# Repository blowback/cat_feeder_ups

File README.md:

# UPS for SureFeed Microchip Pet Feeder Connect

The feeder takes 4 'C' cell batteries. I have 7 feeders. Alkaline batteries 
get expensive real fast and murder the planet, and NiMH cells take an age to 
charge - you spend your whole life swapping batteries in and out of the charger.

The plan: build a miniature UPS that fits inside one of the 2xC-cell battery compartments,
and use it to maintain a 26650 LiPo in the other. Each feeder will be essentially 
mains powered (via a USB adaptor) most of the time: in the event of a power outage 
it will fail over to the battery, which should be sufficient to run it for a couple 
of weeks if necessary.

The other beauty of this approach: the battery has the capacity to handle the current 
draw (inrush and steady-state) when the motor is operating.

## Power consumption analysis

NiCad C cells are nominally 1.2V, so the pack is 4.8V nominal. At 5000mAh rated 
(let's be realistic and call it 2500mAh) and a two-week runtime, we can work out the average current draw:

Energy budget per feeder:

Pack energy: 4.8V × 2.5Ah = 12 Wh realistic
Runtime: 14 days = 336 hours
Average power: 12 Wh / 336 h ≈ 36 mW average
Average current at 4.8V: ≈ 7.5 mA average

**Average** current during motor operation was measured at 250 mA (cheap-ass bench PSU) - 
the peak current is probably 5x that.

## Physical constraints

A standard C cell is:

Diameter: 26.2mm
Length: 50.0mm

Each "slot" holds 2 × C cells stacked = 100mm long × 26.2mm diameter. 

With two slots side by side we have a compartment roughly 100mm deep × ~60mm wide × ~30mm tall (the slots sit in a tray).

### The slot geometry, precisely:

26 mm diameter circular cross-section (C-cell slot)
The usable PCB width isn't 26 mm — it's the chord of that circle at whatever depth the PCB sits. 
If the PCB sits centrally, the usable rectangle inscribed in a 26 mm circle is about 
22 mm wide × 22 mm tall, but since the slot is deep (100 mm) and we're filling it lengthwise, 
we treat the cross-section as a constraint on width only. Realistically 22 mm safe width, 
with the PCB sitting in the bottom of the cylindrical channel.

Length: 90 mm available (100 mm slot minus ~10 mm for wiring clearance to the cell)
Height (component clearance above PCB): roughly 8–10 mm before we hit the slot wall curvature

So we can't afford any big electrolytics or inductors.

## LiPo backup capacity in one C-cell slot:

A single-cell LiPo fits in one C-cell bay (≤26mm diameter, ≤100mm long) — 
cylindrical 26650 LiPo cells are 26mm × 65mm, giving around 4000–5000 mAh at 3.7V nominal = ~15–18 Wh. 

That's actually more energy than the current NiCadx! 

A flat pouch LiPo of similar volume would also work and might be easier to source (e.g. a 103450 or similar).

At 36mW average draw, a 5000mAh/3.7V LiPo = 18.5 Wh → 18.5 Wh ÷ 0.036 W ≈ 514 hours ≈ 21 days of backup. Nice.

Cat biscuits will have run out long before that!

## Proposed architecture

- a LiPo charge controller with "power path" management so that we can use the battery's capacity to absorb motor current demandss
- a boost convertor to boost the LiPo up to 5v. 

## Device selection 

After many, many false starts:

 - BQ24079  for the LiPo controller
 - TPS61235P boost convertor - fixed 5.1v output  and very minimal component controller
 - SPM5020T-1R0M inductor from TDK: nice and compact: 5x2mm, 11A Isat. 

 Those packages are all quite fiddly, and we'll prolly have to go to 0402 for the discretes. 
Maybe time to experiment with having a boardhouse stuff the board!  I'm thinking JLCB...

## JLPCB substitutions

- L1: was C408536 now C695604
- U2: was unspecified! now C140287 (has no SYSOFF pin, but is same package with a NC pad so no schematic/pcb change)
- J1: was C173752 - shouldn't be in BOM (is thru-hole)
- D2: was C2286 (RED) but we want GREEN so -> C12624
- R4, R6: wrong part, need 1.5k 0402 -> C114759
- R5: wrong part, need 10k 0402 -> C60490
- R7: wrong part, need 1.18k -> C3016052
- R8: wrong part, need 1.13k -> C453521

## JLPCB substitutions (2)

Gah, LED footprints are 0402 but the LCSC part numbers are for 0603!

- D1: (RED) -> C130719
- D2: (GREEN) -> C74338
- R8: was C453521 but JLPCB no-stocky, switching forC67014

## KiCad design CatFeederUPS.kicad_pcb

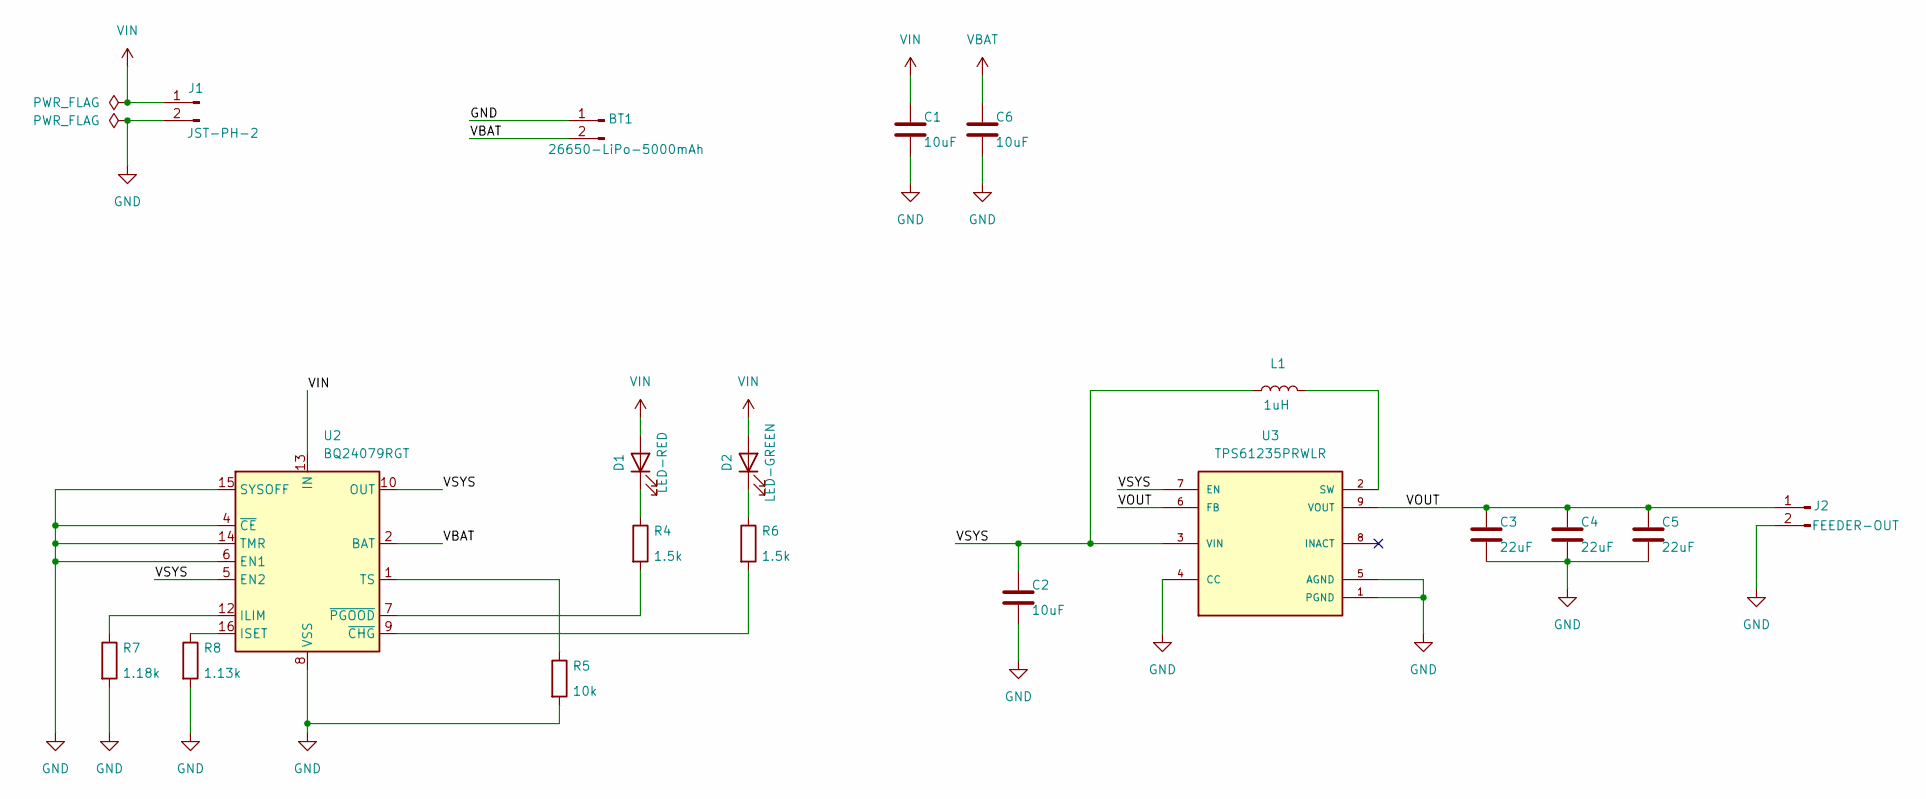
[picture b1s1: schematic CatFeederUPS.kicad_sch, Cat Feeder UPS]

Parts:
BT1: 26650-LiPo-5000mAh; PinHeader_1x02_P2.54mm_Vertical
C1, C6: 10uF; C_0402_1005Metric; Voltage 10V; LCSC C15525
C2: 10uF; C_0402_1005Metric; Voltage 6.3V; LCSC C15525
C3, C4, C5: 22uF; C_0603_1608Metric; Voltage 10V; LCSC C59461
D1: LED-RED; LED_0402_1005Metric; LCSC C130719
D2: LED-GREEN; LED_0402_1005Metric; LCSC C74338
J1: JST-PH-2; JST_PH_S2B-PH-K_1x02_P2.00mm_Horizontal
J2: FEEDER-OUT; PinHeader_1x02_P2.54mm_Vertical
L1: 1uH; IND_SPM5020T-1R0M-LR; LCSC C695604
R4, R6: 1.5k; R_0402_1005Metric; LCSC C114759
R5: 10k; R_0402_1005Metric; LCSC C60490
R7: 1.18k; R_0402_1005Metric; LCSC C3016052
R8: 1.13k; R_0402_1005Metric; LCSC C67014
U2: BQ24079RGT; VQFN-16-1EP_3x3mm_P0.5mm_EP1.6x1.6mm; LCSC C140287
U3: TPS61235PRWLR; CONV_TPS61235PRWLR; DigiKey_Part_Number 296-47376-1-ND

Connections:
/VOUT: C3.1, C4.1, C5.1, J2.1, U3.6 (FB), U3.9 (VOUT)
/VSYS: C2.1, L1.1, U2.5 (EN2), U2.10 (OUT), U2.11 (OUT), U3.3 (VIN), U3.7 (EN)
GND: BT1.1, C1.2, C2.2, C3.2, C4.2, C5.2, C6.2, J1.2, J2.2, R5.2, R7.2, R8.2, U2.4 (~CE), U2.6 (EN1), U2.8 (VSS), U2.14 (TMR), U2.15 (SYSOFF), U2.17 (VSS), U3.1 (PGND), U3.4 (CC), U3.5 (AGND)
unnamed: D1.1 (K), R4.1
unnamed: D2.1 (K), R6.1
unnamed: R7.1, U2.12 (ILIM)
unnamed: R8.1, U2.16 (ISET)
unnamed: R5.1, U2.1 (TS)
unnamed: R6.2, U2.9 (~CHG)
unnamed: R4.2, U2.7 (~PGOOD)
unnamed: L1.2, U3.2 (SW)
VBAT: BT1.2, C6.1, U2.2 (BAT), U2.3 (BAT)
VIN: C1.1, D1.2 (A), D2.2 (A), J1.1, U2.13 (IN)

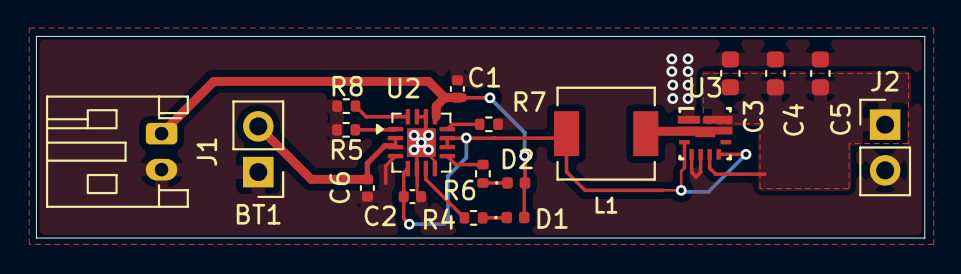
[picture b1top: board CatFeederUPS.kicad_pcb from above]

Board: 2 copper layers, 49.4 x 11.2 mm, 19 parts (0 on the bottom side), 13 nets.

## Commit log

2026-04-01 first commit, schematic captured
2026-04-01 Basic layout done, but...
    There are a lot of problems with the TPW21635P footprint. It's got a
    gigantic pad 2 (SW) that's a weird T-shape, and both the SnapEDA and
    Ultra Librarian footprints represent this as a "polygon" overlaid over
    a "pad", which causes DRC to complain bitterly about both electrical
    overlap and soldermask overlap, which I cannot fix with board setup,
    design rules exceptions etc. etc.
2026-04-01 pcb layout complete
2026-04-01 squish board
2026-04-01 throw some graphics on there
2026-04-01 fix LCSC part numbers, and the goddam TPS61235 footprint **again**
2026-04-01 a couple more component swaps, and away into production we go!
2026-04-02 add some images for the README
2026-04-02 update readme with images
